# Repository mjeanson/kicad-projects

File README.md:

KiCad Projects
==================

Repository Contents
-------------------
* **/layout** - Page layout files.
* **/projects** - The projects.

License Information
-------------------

The hardware is released under [Creative Commons ShareAlike 4.0 International](https://creativecommons.org/licenses/by-sa/4.0/).
The code is beerware; if you see me at the local watering hole, and you've found my code helpful, please buy me a beer!

Distributed as-is; no warranty is given.

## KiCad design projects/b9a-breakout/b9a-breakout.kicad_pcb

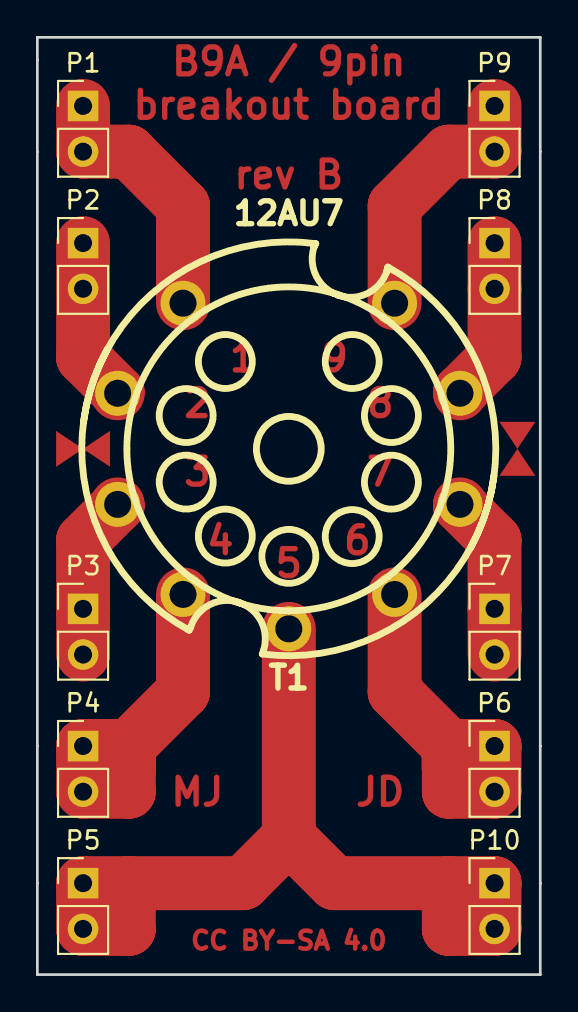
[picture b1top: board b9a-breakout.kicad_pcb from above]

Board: 2 copper layers, 27.9 x 52.1 mm, 11 parts (0 on the bottom side), 9 nets.

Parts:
P1, P2, P3, P4, P5, P6, P7, P8, P9, P10: CONN_01X02; Pin_Header_Straight_1x02_Pitch2.54mm
T1: 12AU7; socket_gzc9-b

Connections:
unnamed: P1.1, P1.2, T1.1
unnamed: P2.1, P2.2, T1.2
unnamed: P3.1, P3.2, T1.3
unnamed: P4.1, P4.2, T1.4
unnamed: P6.1, P6.2, T1.6
unnamed: P7.1, P7.2, T1.7
unnamed: P8.1, P8.2, T1.8
unnamed: P9.1, P9.2, T1.9
unnamed: P5.1, P5.2, P10.1, P10.2, T1.5

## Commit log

2017-02-10 Initial import
2017-02-10 b9a-breakout: Add pdf exports

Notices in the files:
projects/b9a-breakout/b9a-breakout.kicad_pcb:
Released under the Creative Commons Attribution-ShareAlike 4.0 License
CC BY-SA 4.0
